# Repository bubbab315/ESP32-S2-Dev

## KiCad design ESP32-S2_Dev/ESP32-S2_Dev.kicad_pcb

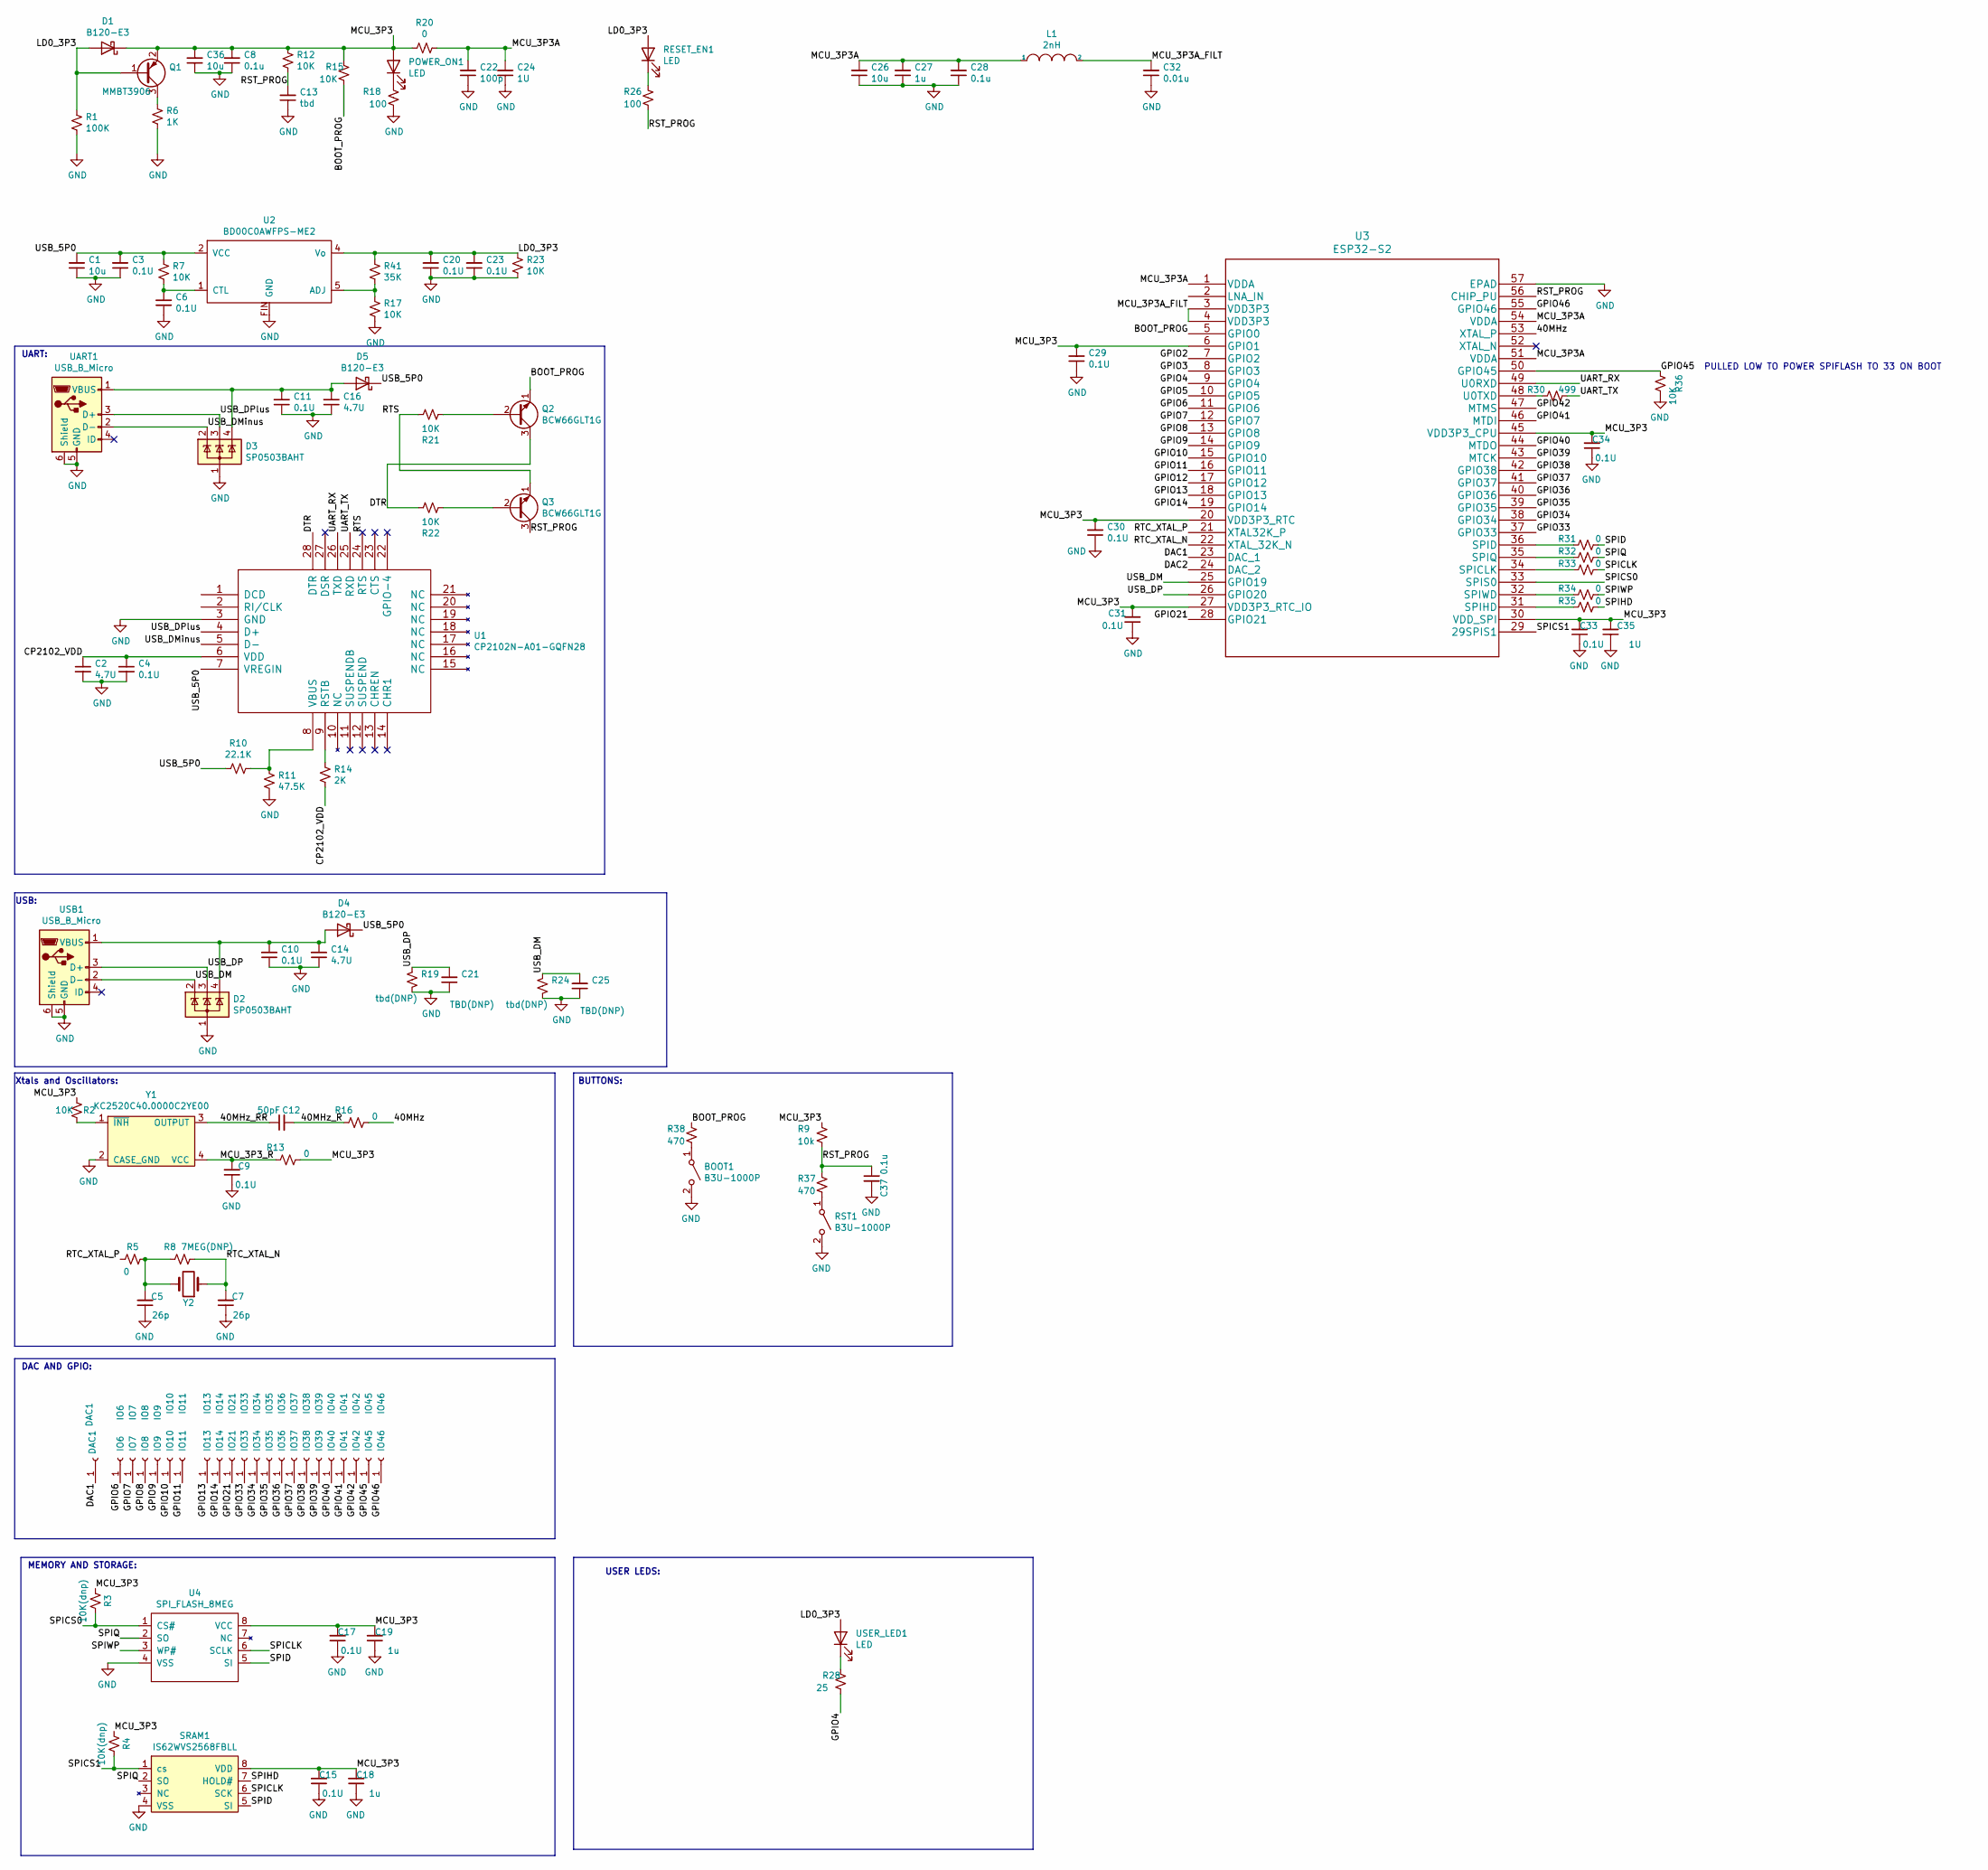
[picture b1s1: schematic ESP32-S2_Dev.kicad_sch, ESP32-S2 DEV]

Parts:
BOOT1: B3U-1000P; SW_SPST_B3U-1000P
C1, C26, C36: 10u; C_0402_1005Metric
C2, C14, C16: 4.7U; C_0402_1005Metric
C3, C4, C6, C9, C10, C11, C15, C17, C20, C23, C29, C30, C31, C33, C34: 0.1U; C_0402_1005Metric
C5, C7: 26p; C_0402_1005Metric
C8, C28, C37: 0.1u; C_0402_1005Metric
C12: 50pF; C_0402_1005Metric
C13: tbd; C_0402_1005Metric
C18, C19, C27: 1u; C_0402_1005Metric
C21, C25: TBD(DNP); C_0402_1005Metric
C22: 100p; C_0402_1005Metric
C24, C35: 1U; C_0402_1005Metric
C32: 0.01u; C_0402_1005Metric
D1, D4, D5: B120-E3; D_SMA
D2, D3: SP0503BAHT; SOT-143
DAC1: DAC1; PinSocket_1x01_P2.54mm_Vertical
IO6: IO6; PinSocket_1x01_P2.54mm_Vertical
IO7: IO7; PinSocket_1x01_P2.54mm_Vertical
IO8: IO8; PinSocket_1x01_P2.54mm_Vertical
IO9: IO9; PinSocket_1x01_P2.54mm_Vertical
IO10: IO10; PinSocket_1x01_P2.54mm_Vertical
IO11: IO11; PinSocket_1x01_P2.54mm_Vertical
IO13: IO13; PinSocket_1x01_P2.54mm_Vertical
IO14: IO14; PinSocket_1x01_P2.54mm_Vertical
IO21: IO21; PinSocket_1x01_P2.54mm_Vertical
IO33: IO33; PinSocket_1x01_P2.54mm_Vertical
IO34: IO34; PinSocket_1x01_P2.54mm_Vertical
IO35: IO35; PinSocket_1x01_P2.54mm_Vertical
IO36: IO36; PinSocket_1x01_P2.54mm_Vertical
IO37: IO37; PinSocket_1x01_P2.54mm_Vertical
IO38: IO38; PinSocket_1x01_P2.54mm_Vertical
IO39: IO39; PinSocket_1x01_P2.54mm_Vertical
IO40: IO40; PinSocket_1x01_P2.54mm_Vertical
IO41: IO41; PinSocket_1x01_P2.54mm_Vertical
IO42: IO42; PinSocket_1x01_P2.54mm_Vertical
IO45: IO45; PinSocket_1x01_P2.54mm_Vertical
IO46: IO46; PinSocket_1x01_P2.54mm_Vertical
L1: 2nH; L_0402_1005Metric
POWER_ON1: LED; LED_0805_2012Metric_Pad1.15x1.40mm_HandSolder
Q1: MMBT3906; SOT-416
Q2, Q3: BCW66GLT1G; SOT-23
R1: 100K; R_0402_1005Metric
R2, R7, R12, R15, R17, R21, R22, R23, R36: 10K; R_0402_1005Metric
R3, R4: 10K(dnp); R_0402_1005Metric
R5, R13, R16, R20, R31, R32, R33, R34, R35: 0; R_0402_1005Metric
R6: 1K; R_0402_1005Metric
R8: 7MEG(DNP); R_0402_1005Metric
R9: 10k; R_0402_1005Metric
R10: 22.1K; R_0402_1005Metric
R11: 47.5K; R_0402_1005Metric
R14: 2K; R_0402_1005Metric
R18, R26: 100; R_0402_1005Metric
R19, R24: tbd(DNP); R_0402_1005Metric
R28: 25; R_0402_1005Metric
R30: 499; R_0402_1005Metric
R37, R38: 470; R_0402_1005Metric
R41: 35K; R_0402_1005Metric
RESET_EN1: LED; LED_0805_2012Metric_Pad1.15x1.40mm_HandSolder
RST1: B3U-1000P; SW_SPST_B3U-1000P
SRAM1: IS62WVS2568FBLL; SOIC-8_3.9x4.9mm_P1.27mm
U1: CP2102N-A01-GQFN28
U2: BD00C0AWFPS-ME2
U3: ESP32-S2
U4: SPI_FLASH_8MEG; USON8(2X3)
UART1: USB_B_Micro; USB_Micro-B_Molex-105017-0001
USB1: USB_B_Micro; USB_Micro-B_Molex-105017-0001
USER_LED1: LED; LED_0603_1608Metric_Pad1.05x0.95mm_HandSolder
Y1: KC2520C40.0000C2YE00
Y2: Crystal; Crystal_SMD_3215-2Pin_3.2x1.5mm

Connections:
/40MHz: R16.2, U3.53 (XTAL_P)
/40MHz_R: C12.2, R16.1
/40MHz_RR: C12.1, Y1.3 (OUTPUT)
/CP2102_VDD: C2.1, C4.1, R14.1, U1.6 (VDD)
/DAC1: DAC1.1, U3.23 (DAC_1)
/DAC2: U3.24 (DAC_2)
/GPIO2: U3.7 (GPIO2)
/GPIO3: U3.8 (GPIO3)
/GPIO4: R28.1, U3.9 (GPIO4)
/GPIO5: U3.10 (GPIO5)
/GPIO6: IO6.1, U3.11 (GPIO6)
/GPIO7: IO7.1, U3.12 (GPIO7)
/GPIO8: IO8.1, U3.13 (GPIO8)
/GPIO9: IO9.1, U3.14 (GPIO9)
/GPIO10: IO10.1, U3.15 (GPIO10)
/GPIO11: IO11.1, U3.16 (GPIO11)
/GPIO12: U3.17 (GPIO12)
/GPIO13: IO13.1, U3.18 (GPIO13)
/GPIO14: IO14.1, U3.19 (GPIO14)
/GPIO21: IO21.1, U3.28 (GPIO21)
/GPIO33: IO33.1, U3.37 (GPIO33)
/GPIO34: IO34.1, U3.38 (GPIO34)
/GPIO35: IO35.1, U3.39 (GPIO35)
/GPIO36: IO36.1, U3.40 (GPIO36)
/GPIO37: IO37.1, U3.41 (GPIO37)
/GPIO38: IO38.1, U3.42 (GPIO38)
/GPIO39: IO39.1, U3.43 (MTCK)
/GPIO40: IO40.1, U3.44 (MTDO)
/GPIO41: IO41.1, U3.46 (MTDI)
/GPIO42: IO42.1, U3.47 (MTMS)
/GPIO45: IO45.1, R36.1, U3.50 (GPIO45)
/GPIO46: IO46.1, U3.55 (GPIO46)
/LD0_3P3: C20.2, C23.2, D1.2 (A), Q1.1 (B), R1.2, R23.2, R41.2, RESET_EN1.2 (A), U2.4 (Vo), USER_LED1.2 (A)
/MCU_3P3: C8.2, C15.2, C17.2, C18.2, C19.2, C29.2, C30.2, C31.2, C33.2, C34.2, C35.2, C36.2, D1.1 (K), POWER_ON1.2 (A), Q1.2 (E), R2.2, R3.1, R4.1, R9.2, R12.2, R13.2, R15.2, R20.1, SRAM1.8 (VDD), U3.6 (GPIO1), U3.20 (VDD3P3_RTC), U3.27 (VDD3P3_RTC_IO), U3.30 (VDD_SPI), U3.45 (VDD3P3_CPU), U4.8 (VCC)
/MCU_3P3A: C22.2, C24.2, C26.2, C27.2, C28.2, L1.1, R20.2, U3.1 (VDDA), U3.51 (VDDA), U3.54 (VDDA)
/MCU_3P3A_FILT: C32.2, L1.2, U3.3 (VDD3P3), U3.4 (VDD3P3)
/MCU_3P3_R: C9.2, R13.1, Y1.4 (VCC)
/RST_PROG: C13.2, C37.1, Q3.3 (C), R9.1, R12.1, R26.1, R37.2, U3.56 (CHIP_PU)
/RTC_XTAL_N: C7.2, R8.2, U3.22 (XTAL_32K_N), Y2.1
/RTC_XTAL_P: R5.1, U3.21 (XTAL32K_P)
/SPICLK: R33.2, SRAM1.6 (SCK), U4.6 (SCLK)
/SPICS0: R3.2, U3.33 (SPIS0), U4.1 (CS#)
/SPICS1: R4.2, SRAM1.1 (cs), U3.29 (29SPIS1)
/SPID: R31.2, SRAM1.5 (SI), U4.5 (SI)
/SPIHD: R35.2, SRAM1.7 (HOLD#)
/SPIQ: R32.2, SRAM1.2 (SO), U4.2 (SO)
/SPIWP: R34.2, U4.3 (WP#)
/UART_RX: U1.26 (TXD), U3.49 (U0RXD)
/UART_TX: R30.2, U1.25 (RXD)
/USB_5P0: C1.2, C3.2, D4.1 (K), D5.1 (K), R7.2, R10.1, U1.7 (VREGIN), U2.2 (VCC)
/USB_DM: C25.2, D2.2 (K), R24.1, U3.25 (GPIO19), USB1.2 (D-)
/USB_DMinus: D3.2 (K), U1.5 (D-), UART1.2 (D-)
/USB_DP: C21.2, D2.3 (K), R19.1, U3.26 (GPIO20), USB1.3 (D+)
/USB_DPlus: D3.3 (K), U1.4 (D+), UART1.3 (D+)
GND: BOOT1.2 (B), C1.1, C2.2, C3.1, C4.2, C5.1, C6.1, C7.1, C8.1, C9.1, C10.1, C11.1, C13.1, C14.1, C15.1, C16.1, C17.1, C18.1, C19.1, C20.1, C21.1, C22.1, C23.1, C24.1, C25.1, C26.1, C27.1, C28.1, C29.1, C30.1, C31.1, C32.1, C33.1, C34.1, C35.1, C36.1, C37.2, D2.1 (A), D3.1 (A), R1.1, R6.1, R11.1, R17.1, R18.1, R19.2, R23.1, R24.2, R36.2, RST1.2 (B), SRAM1.4 (VSS), U1.3 (GND), U2.FIN (GND), U3.57 (EPAD), U4.4 (VSS), UART1.5 (GND), UART1.6 (Shield), USB1.5 (GND), USB1.6 (Shield), Y1.2 (CASE_GND)
unnamed: BOOT1.1 (A), R38.1
unnamed: C5.2, R5.2, R8.1, Y2.2
unnamed: C6.2, R7.1, U2.1 (CTL)
unnamed: C10.2, C14.2, D2.4 (K), D4.2 (A), USB1.1 (VBUS)
unnamed: C11.2, C16.2, D3.4 (K), D5.2 (A), UART1.1 (VBUS)
unnamed: POWER_ON1.1 (K), R18.2
unnamed: Q1.3 (C), R6.2
unnamed: Q2.2 (B), R21.1
unnamed: Q3.2 (B), R22.1
unnamed: R2.1, Y1.1 (~INH)
unnamed: R10.2, R11.2, U1.8 (VBUS)
unnamed: R14.2, U1.9 (RSTB)
unnamed: R17.2, R41.1, U2.5 (ADJ)
unnamed: R26.2, RESET_EN1.1 (K)
unnamed: R28.2, USER_LED1.1 (K)
unnamed: R30.1, U3.48 (U0TXD)
unnamed: R31.1, U3.36 (SPID)
unnamed: R32.1, U3.35 (SPIQ)
unnamed: R33.1, U3.34 (SPICLK)
unnamed: R34.1, U3.32 (SPIWD)
unnamed: R35.1, U3.31 (SPIHD)
unnamed: R37.1, RST1.1 (A)

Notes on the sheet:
UART:
BUTTONS:
USB:
USER LEDS:
MEMORY AND STORAGE:
PULLED LOW TO POWER SPIFLASH TO 33 ON BOOT
Xtals and Oscillators:
DAC AND GPIO:

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
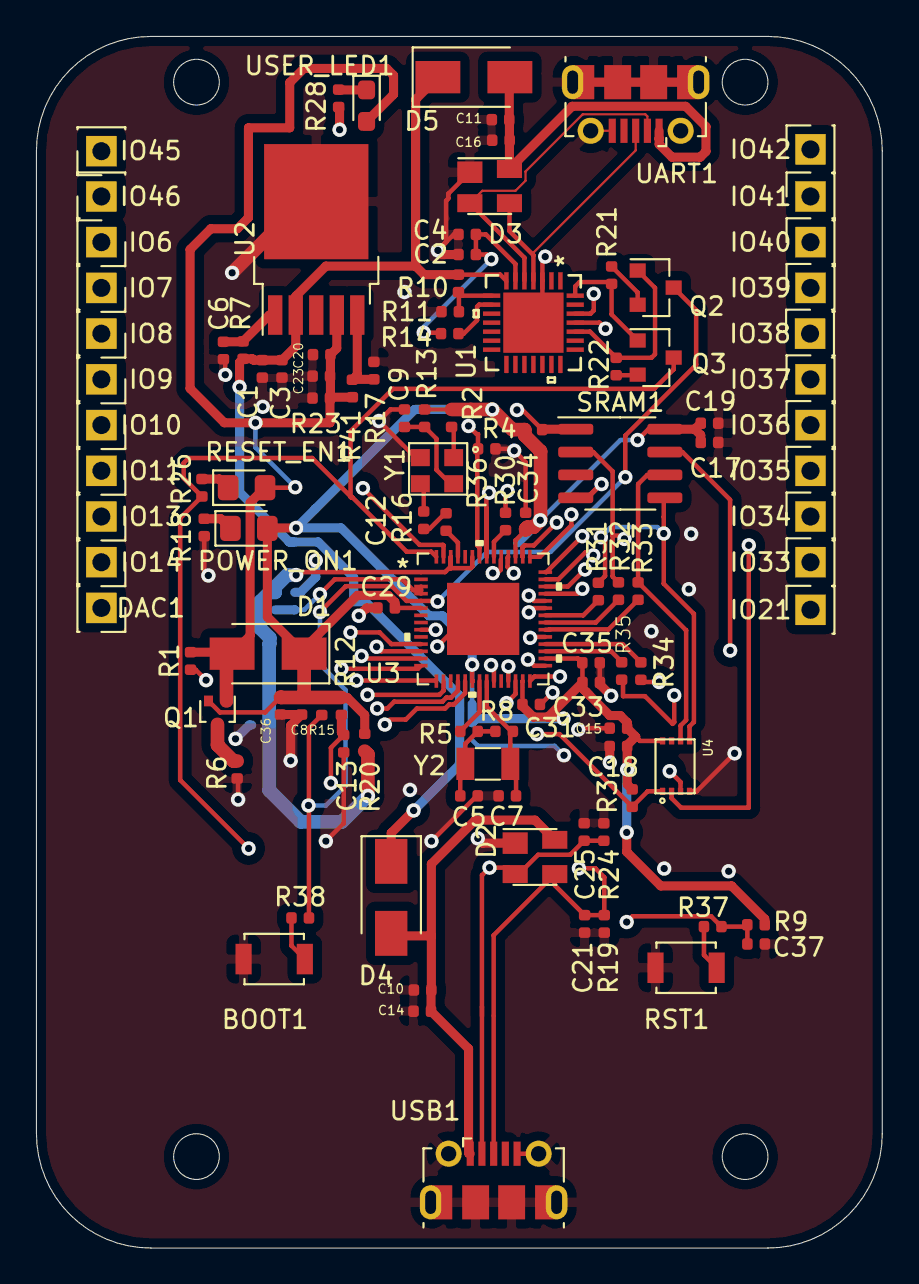
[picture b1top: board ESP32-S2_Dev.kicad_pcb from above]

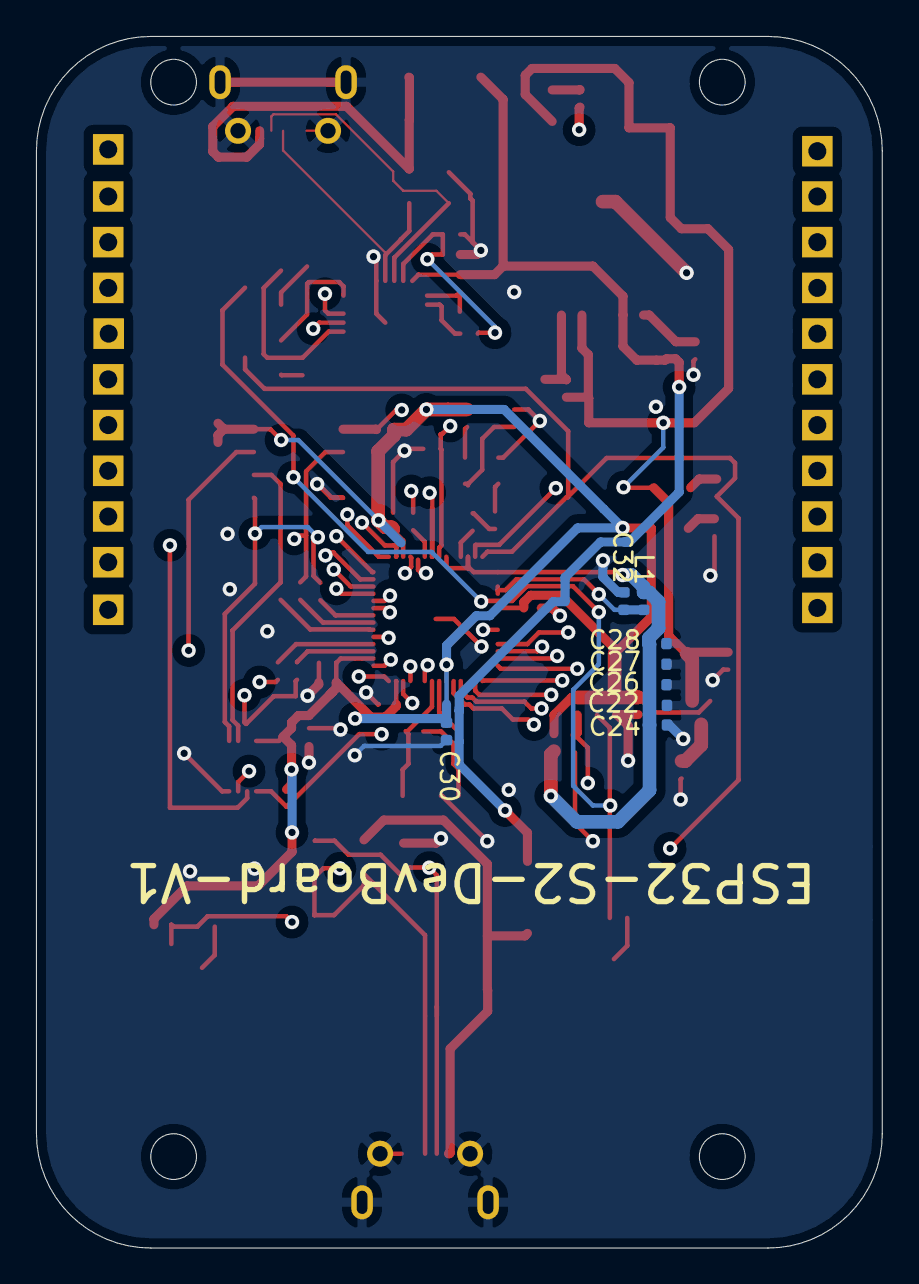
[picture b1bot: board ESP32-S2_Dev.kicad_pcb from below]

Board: 4 copper layers, 47.0 x 67.3 mm, 118 parts (8 on the bottom side), 75 nets.

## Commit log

2022-05-19 adding files to repo
2022-05-19 added schematic pdf and put gerber pdf in folder
2022-06-08 updated layout to move usb connectors closer to the edges, as they are today pluggin in will be nigh impossible.
2022-06-15 fixed the oscillator footprint mirror issue, made Q1 a SOT416, and added power input diodes
2022-06-15 connected a net on the back for power
2022-06-17 fixed RTS and DTR and added them as well as the reset timing capacitors to the layout
2022-06-17 changed flash to gigadevice, since microchip is not supported
2022-06-23 changed bom part numbers to reduce price, removed some parts that aren't strictly required
2022-07-01 Create readme.txt
    added a readme to be filled in
2023-07-21 fixed the autoprogram circuit

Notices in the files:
parts and their libraries:
Copyright 2021 Accelerated Designs. All rights reserved.
Copyright 2016 Accelerated Designs. All rights reserved.
